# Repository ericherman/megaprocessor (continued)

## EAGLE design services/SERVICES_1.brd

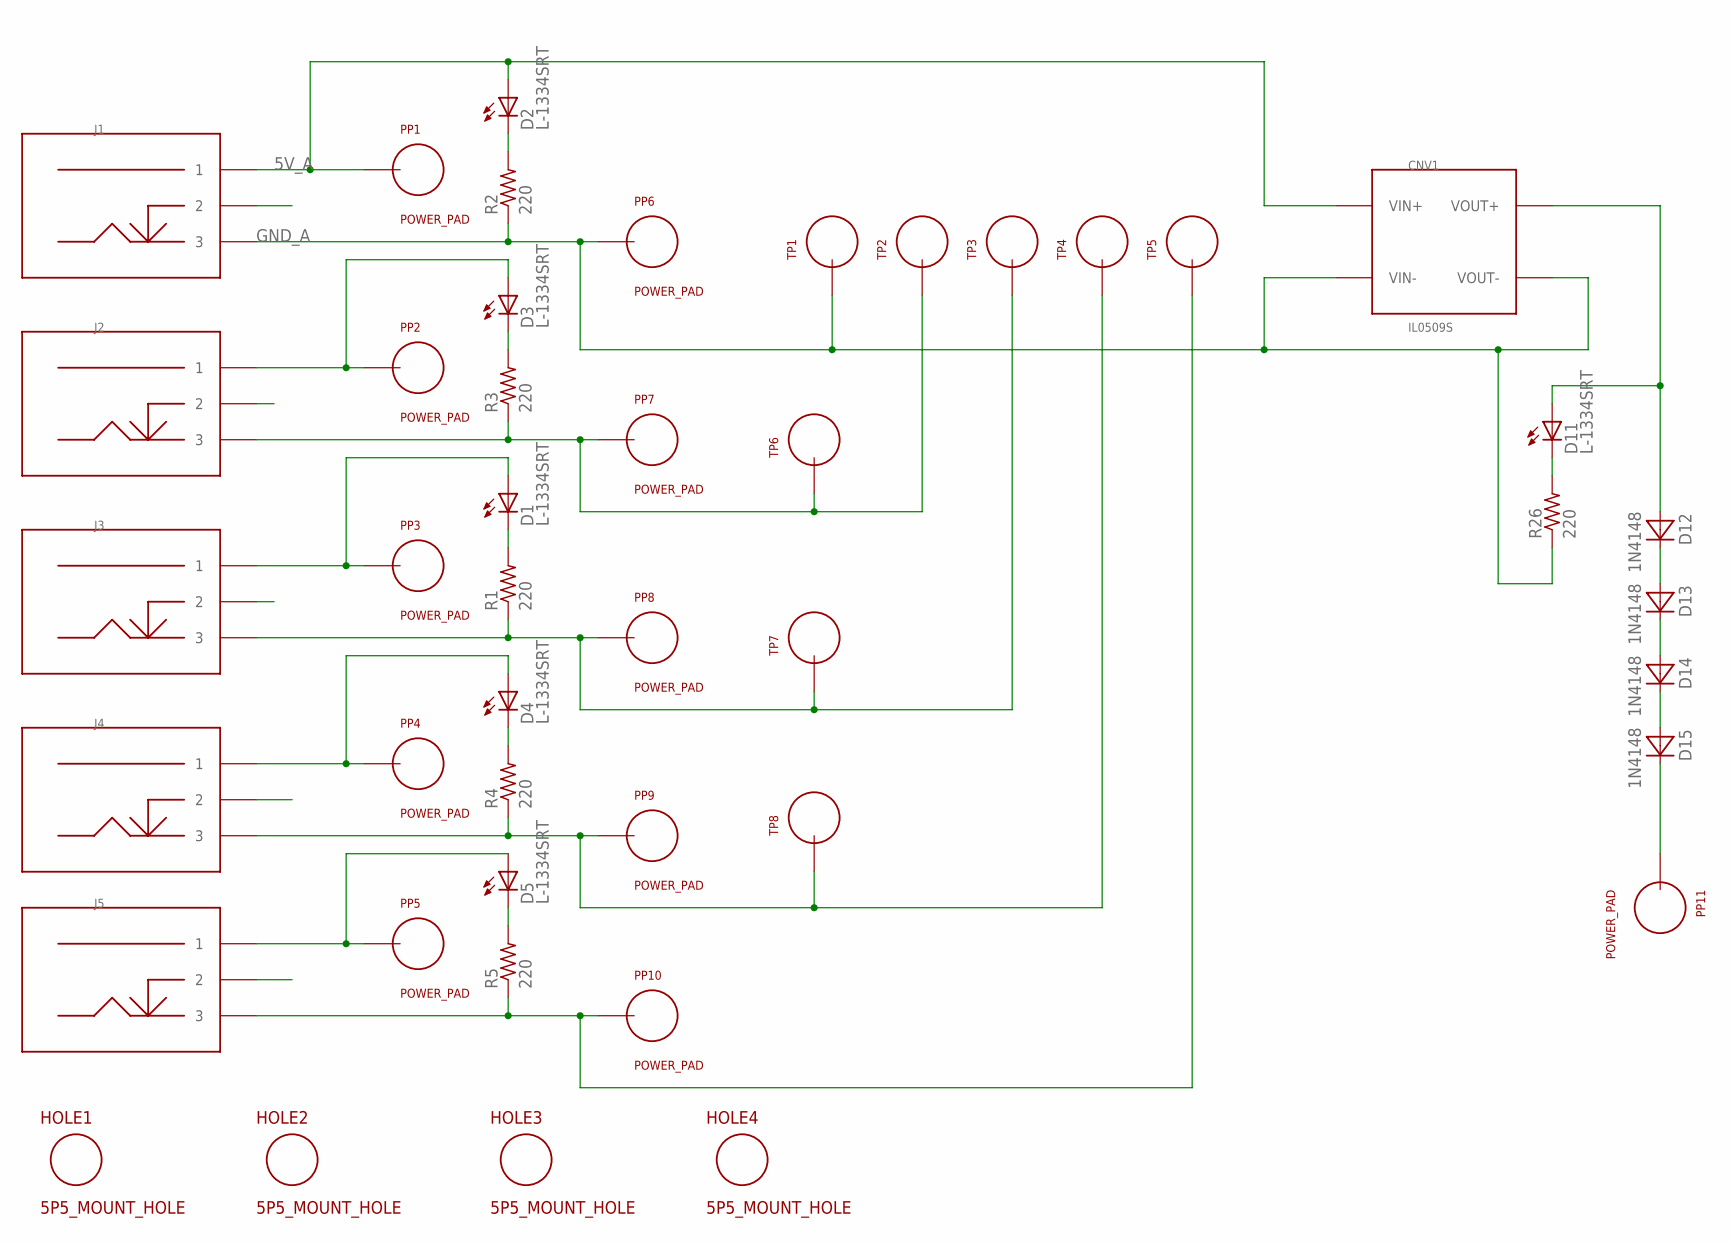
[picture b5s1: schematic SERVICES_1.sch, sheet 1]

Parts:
CNV1: IL0509S; SIL_IL
D1, D2, D3, D4, D5, D11: L-1334SRT; LED3MM
D12, D13, D14, D15: 1N4148; DO34-5
HOLE1, HOLE2, HOLE3, HOLE4: 5P5_MOUNT_HOLE; 5P5M_HOLE
J1, J2, J3, J4, J5: POWER_ENTRY; POWER_25
PP1, PP2, PP3, PP4, PP5, PP6, PP7, PP8, PP9, PP10, PP11: POWER_PAD
R1, R2, R3, R4, R5, R26: 220; R_P2INCH
TP1, TP2, TP3, TP4, TP5, TP6, TP7, TP8: TEST_LOOP

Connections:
5V_A: CNV1.VIN+, D2.A, J1.1, PP1.1; also elsewhere on the board
GND_A: CNV1.VIN-, CNV1.VOUT-, J1.3, PP6.1, R2.1, R26.1, TP1.P$1; also elsewhere on the board
unnamed: D3.A, J2.1, PP2.1
unnamed: D1.A, J3.1, PP3.1
unnamed: D4.A, J4.1, PP4.1
unnamed: D5.A, J5.1, PP5.1
unnamed: J2.3, PP7.1, R3.1, TP2.P$1, TP6.P$1
unnamed: J3.3, PP8.1, R1.1, TP3.P$1, TP7.P$1
unnamed: J4.3, PP9.1, R4.1, TP4.P$1, TP8.P$1
unnamed: J5.3, PP10.1, R5.1, TP5.P$1
unnamed: CNV1.VOUT+, D11.A, D12.A
unnamed: D1.K (C), R1.2
unnamed: D2.K (C), R2.2
unnamed: D3.K (C), R3.2
unnamed: D4.K (C), R4.2
unnamed: D5.K (C), R5.2
unnamed: D11.K (C), R26.2
unnamed: D12.C, D13.A
unnamed: D13.C, D14.A
unnamed: D14.C, D15.A
unnamed: D15.C, PP11.1

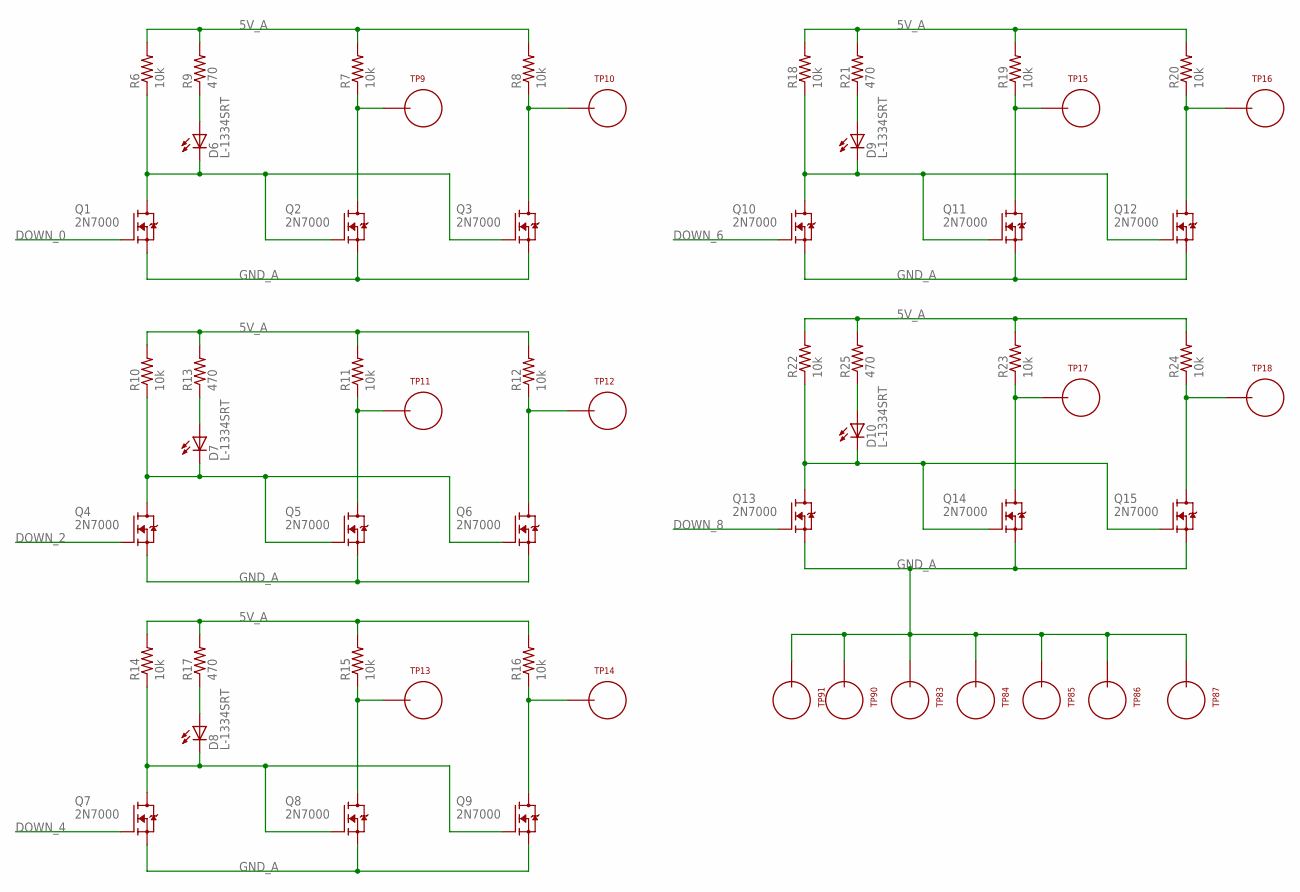
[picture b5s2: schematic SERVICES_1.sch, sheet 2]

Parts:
D6, D7, D8, D9, D10: L-1334SRT; LED3MM
Q1, Q2, Q3, Q4, Q5, Q6, Q7, Q8, Q9, Q10, Q11, Q12, Q13, Q14, Q15: 2N7000; TO92-DGS
R6, R7, R8, R10, R11, R12, R14, R15, R16, R18, R19, R20, R22, R23, R24: 10k; R_P2INCH
R9, R13, R17, R21, R25: 470; R_P2INCH
TP9, TP10, TP11, TP12, TP13, TP14, TP15, TP16, TP17, TP18, TP83, TP84, TP85, TP86, TP87, TP90, TP91: TEST_LOOP

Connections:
5V_A: R6.2, R7.2, R8.2, R9.2, R10.2, R11.2, R12.2, R13.2, R14.2, R15.2, R16.2, R17.2, R18.2, R19.2, R20.2, R21.2, R22.2, R23.2, R24.2, R25.2; also elsewhere on the board
DOWN_0: Q1.G; also elsewhere on the board
DOWN_2: Q4.G; also elsewhere on the board
DOWN_4: Q7.G; also elsewhere on the board
DOWN_6: Q10.G; also elsewhere on the board
DOWN_8: Q13.G; also elsewhere on the board
GND_A: Q1.S, Q2.S, Q3.S, Q4.S, Q5.S, Q6.S, Q7.S, Q8.S, Q9.S, Q10.S, Q11.S, Q12.S, Q13.S, Q14.S, Q15.S, TP83.P$1, TP84.P$1, TP85.P$1, TP86.P$1, TP87.P$1, TP90.P$1, TP91.P$1; also elsewhere on the board
unnamed: D7.A, R13.1
unnamed: Q5.D, R11.1, TP11.P$1
unnamed: Q6.D, R12.1, TP12.P$1
unnamed: D6.A, R9.1
unnamed: Q2.D, R7.1, TP9.P$1
unnamed: Q3.D, R8.1, TP10.P$1
unnamed: D6.K (C), Q1.D, Q2.G, Q3.G, R6.1
unnamed: D7.K (C), Q4.D, Q5.G, Q6.G, R10.1
unnamed: D8.A, R17.1
unnamed: Q8.D, R15.1, TP13.P$1
unnamed: Q9.D, R16.1, TP14.P$1
unnamed: D8.K (C), Q7.D, Q8.G, Q9.G, R14.1
unnamed: D9.A, R21.1
unnamed: Q11.D, R19.1, TP15.P$1
unnamed: Q12.D, R20.1, TP16.P$1
unnamed: D9.K (C), Q10.D, Q11.G, Q12.G, R18.1
unnamed: D10.A, R25.1
unnamed: Q14.D, R23.1, TP17.P$1
unnamed: Q15.D, R24.1, TP18.P$1
unnamed: D10.K (C), Q13.D, Q14.G, Q15.G, R22.1

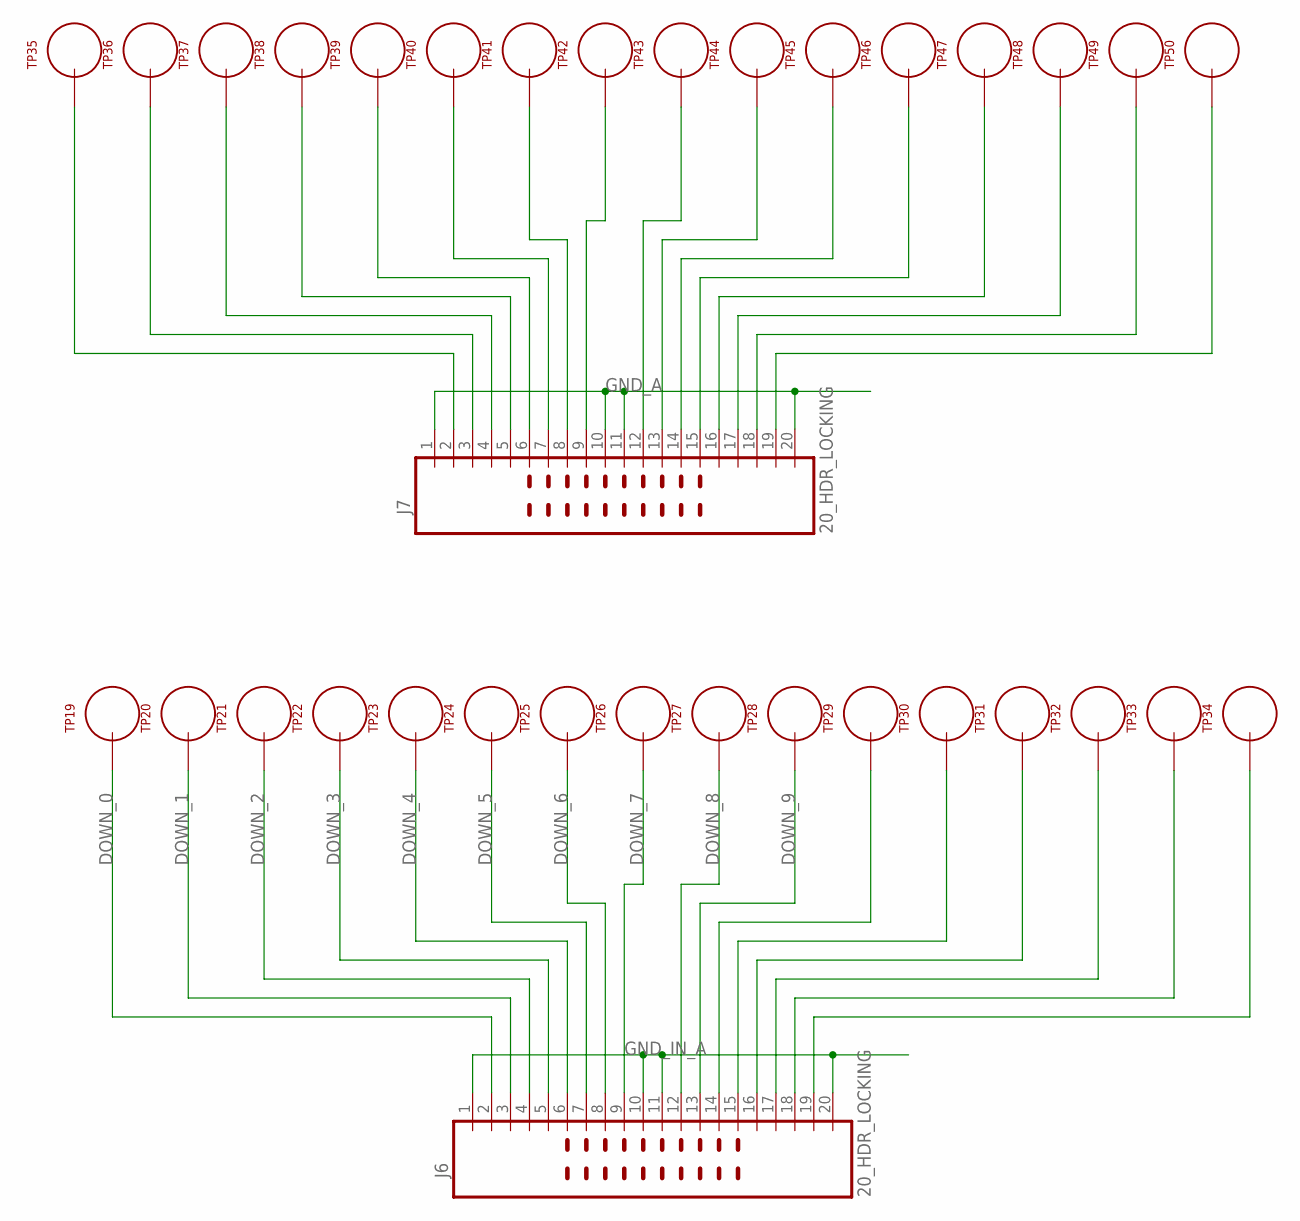
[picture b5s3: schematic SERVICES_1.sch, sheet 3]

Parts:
J6, J7: 20_HDR_LOCKING
TP19, TP20, TP21, TP22, TP23, TP24, TP25, TP26, TP27, TP28, TP29, TP30, TP31, TP32, TP33, TP34, TP35, TP36, TP37, TP38, TP39, TP40, TP41, TP42, TP43, TP44, TP45, TP46, TP47, TP48, TP49, TP50: TEST_LOOP

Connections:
DOWN_0: J6.2, TP19.P$1; also elsewhere on the board
DOWN_1: J6.3, TP20.P$1
DOWN_2: J6.4, TP21.P$1; also elsewhere on the board
DOWN_3: J6.5, TP22.P$1
DOWN_4: J6.6, TP23.P$1; also elsewhere on the board
DOWN_5: J6.7, TP24.P$1
DOWN_6: J6.8, TP25.P$1; also elsewhere on the board
DOWN_7: J6.9, TP26.P$1
DOWN_8: J6.12, TP27.P$1; also elsewhere on the board
DOWN_9: J6.13, TP28.P$1
GND_A: J7.1, J7.10, J7.11, J7.20; also elsewhere on the board
GND_IN_A: J6.1, J6.10, J6.11, J6.20
unnamed: J6.19, TP34.P$1
unnamed: J6.18, TP33.P$1
unnamed: J6.17, TP32.P$1
unnamed: J6.16, TP31.P$1
unnamed: J6.15, TP30.P$1
unnamed: J6.14, TP29.P$1
unnamed: J7.2, TP35.P$1
unnamed: J7.3, TP36.P$1
unnamed: J7.4, TP37.P$1
unnamed: J7.5, TP38.P$1
unnamed: J7.6, TP39.P$1
unnamed: J7.7, TP40.P$1
unnamed: J7.8, TP41.P$1
unnamed: J7.19, TP50.P$1
unnamed: J7.18, TP49.P$1
unnamed: J7.17, TP48.P$1
unnamed: J7.16, TP47.P$1
unnamed: J7.15, TP46.P$1
unnamed: J7.14, TP45.P$1
unnamed: J7.13, TP44.P$1
unnamed: J7.12, TP43.P$1
unnamed: J7.9, TP42.P$1

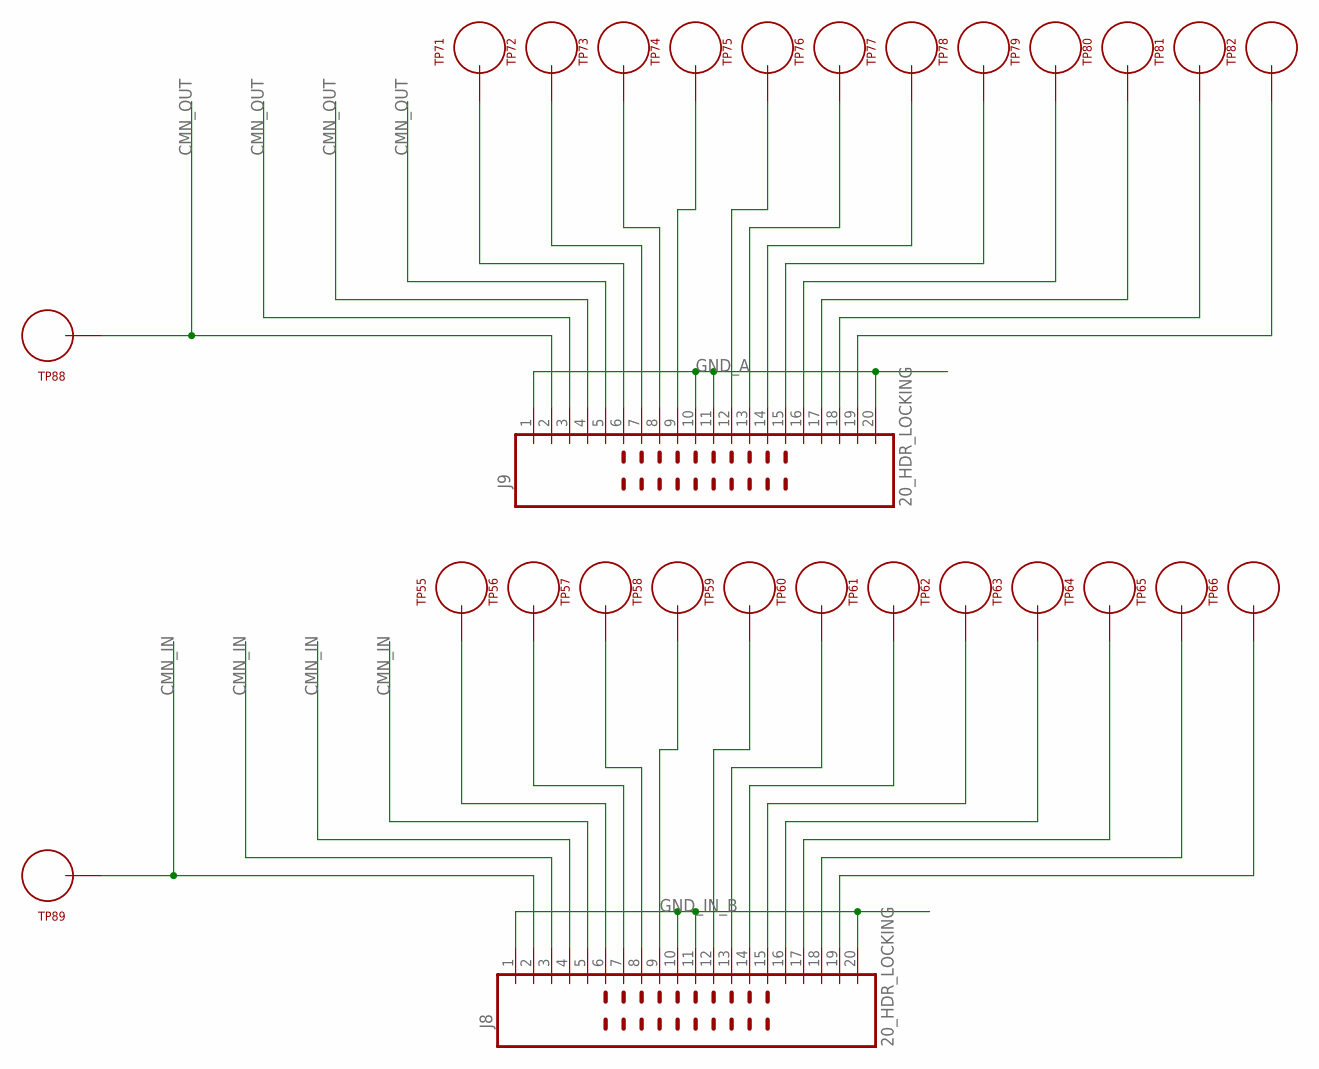
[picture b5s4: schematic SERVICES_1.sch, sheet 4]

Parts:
J8, J9: 20_HDR_LOCKING
TP55, TP56, TP57, TP58, TP59, TP60, TP61, TP62, TP63, TP64, TP65, TP66, TP71, TP72, TP73, TP74, TP75, TP76, TP77, TP78, TP79, TP80, TP81, TP82, TP88, TP89: TEST_LOOP

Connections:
CMN_IN: J8.2, J8.3, J8.4, J8.5, TP89.P$1
CMN_OUT: J9.2, J9.3, J9.4, J9.5, TP88.P$1
GND_A: J9.1, J9.10, J9.11, J9.20; also elsewhere on the board
GND_IN_B: J8.1, J8.10, J8.11, J8.20
unnamed: J8.6, TP55.P$1
unnamed: J8.7, TP56.P$1
unnamed: J8.8, TP57.P$1
unnamed: J8.19, TP66.P$1
unnamed: J8.18, TP65.P$1
unnamed: J8.17, TP64.P$1
unnamed: J8.16, TP63.P$1
unnamed: J8.15, TP62.P$1
unnamed: J8.14, TP61.P$1
unnamed: J8.13, TP60.P$1
unnamed: J8.12, TP59.P$1
unnamed: J8.9, TP58.P$1
unnamed: J9.6, TP71.P$1
unnamed: J9.7, TP72.P$1
unnamed: J9.8, TP73.P$1
unnamed: J9.19, TP82.P$1
unnamed: J9.18, TP81.P$1
unnamed: J9.17, TP80.P$1
unnamed: J9.16, TP79.P$1
unnamed: J9.15, TP78.P$1
unnamed: J9.14, TP77.P$1
unnamed: J9.13, TP76.P$1
unnamed: J9.12, TP75.P$1
unnamed: J9.9, TP74.P$1

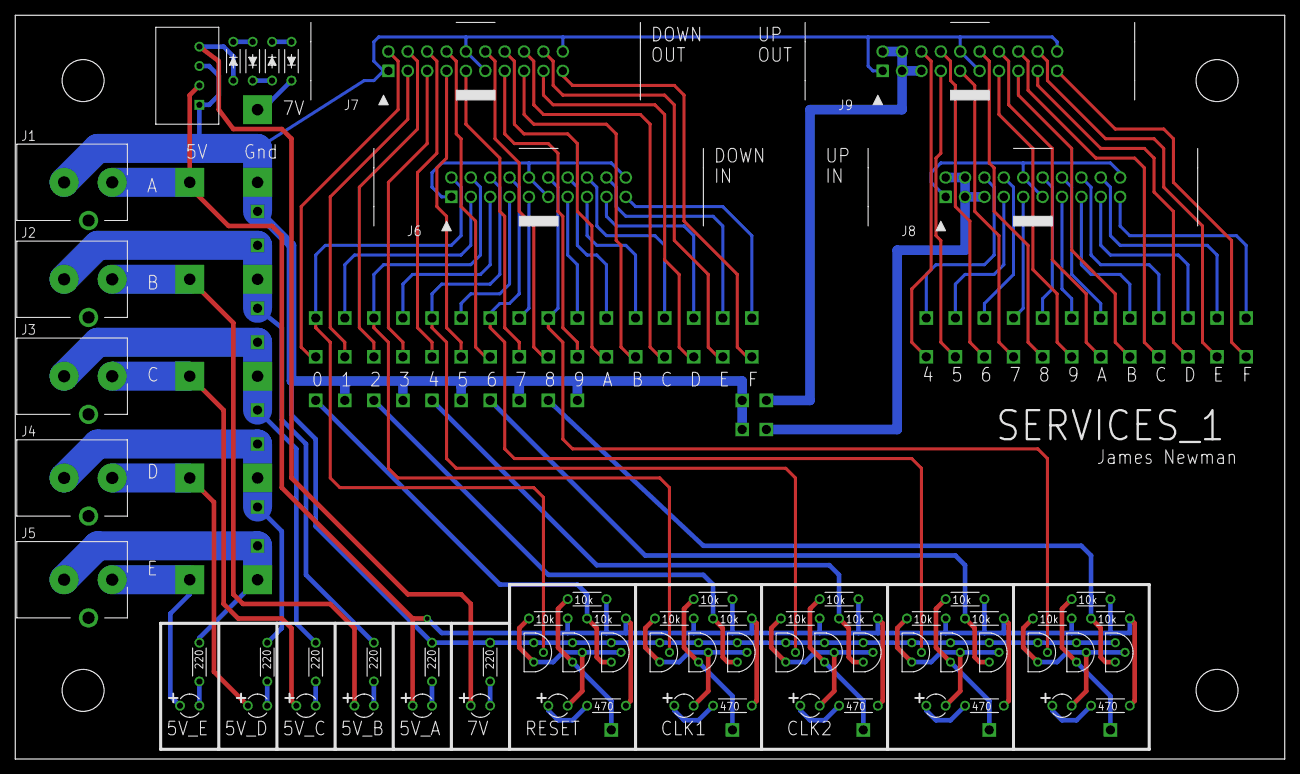
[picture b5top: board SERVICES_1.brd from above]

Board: 2 copper layers, 166.3 x 97.5 mm, 164 parts (0 on the bottom side), 101 nets.

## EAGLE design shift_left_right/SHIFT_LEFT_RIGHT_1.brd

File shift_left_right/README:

Shifter

The shifting is just by wiring from one connector to the other with an
offset. Depending on which side you call the input and which the output
its a left or right shifter. It also generates some status data (is zero
etc).

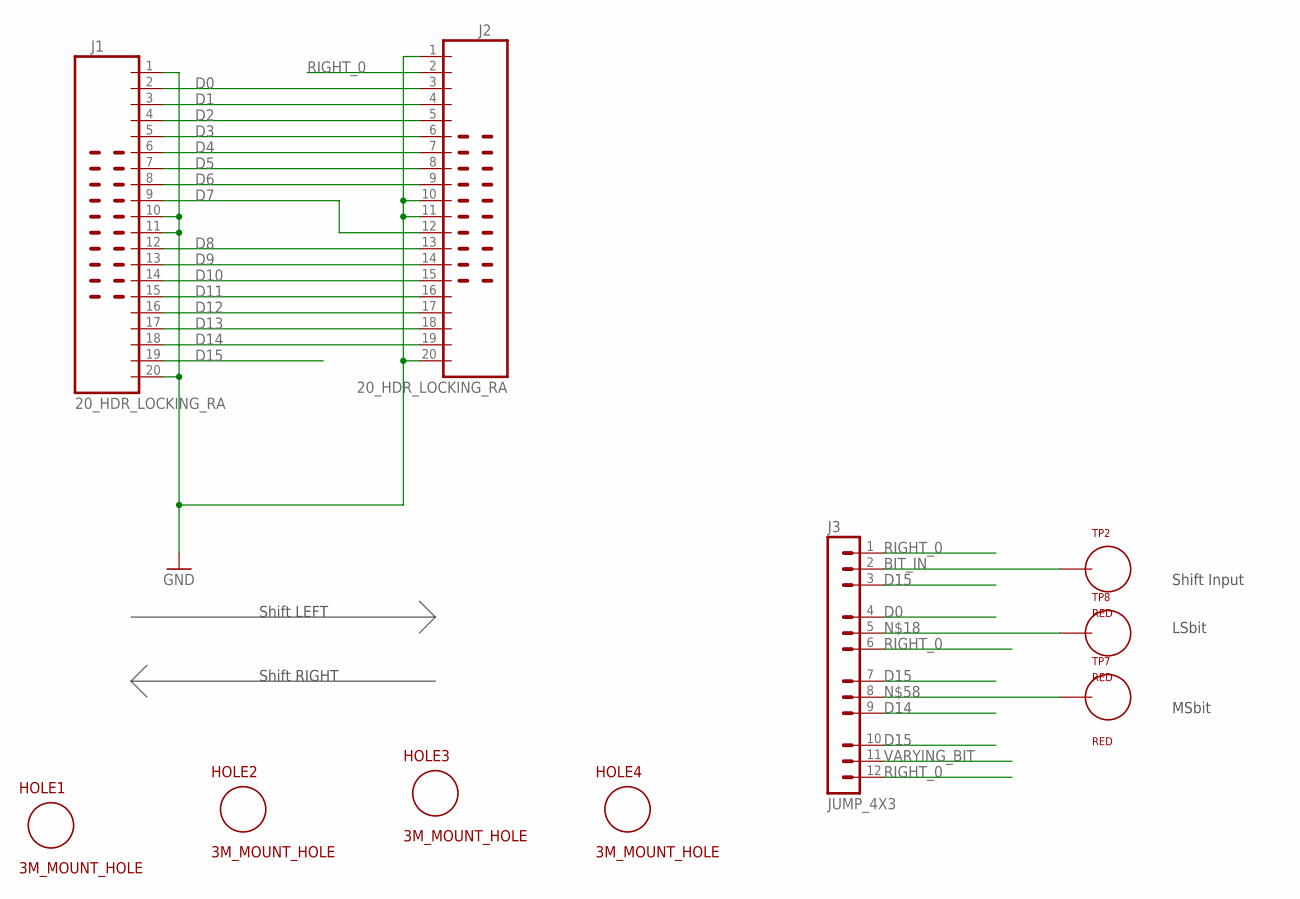
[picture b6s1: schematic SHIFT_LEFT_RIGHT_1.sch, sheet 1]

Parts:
HOLE1, HOLE2, HOLE3, HOLE4: 3M_MOUNT_HOLE; 3M_HOLE
J1, J2: 20_HDR_LOCKING_RA
J3: JUMP_4X3
TP2, TP7, TP8: RED; TEST_LOOP

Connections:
BIT_IN: J3.2, TP2.P$1; also elsewhere on the board
D0: J1.2, J2.3, J3.4; also elsewhere on the board
D1: J1.3, J2.4; also elsewhere on the board
D2: J1.4, J2.5; also elsewhere on the board
D3: J1.5, J2.6; also elsewhere on the board
D4: J1.6, J2.7; also elsewhere on the board
D5: J1.7, J2.8; also elsewhere on the board
D6: J1.8, J2.9; also elsewhere on the board
D7: J1.9, J2.12; also elsewhere on the board
D8: J1.12, J2.13; also elsewhere on the board
D9: J1.13, J2.14; also elsewhere on the board
D10: J1.14, J2.15; also elsewhere on the board
D11: J1.15, J2.16; also elsewhere on the board
D12: J1.16, J2.17; also elsewhere on the board
D13: J1.17, J2.18; also elsewhere on the board
D14: J1.18, J2.19, J3.9; also elsewhere on the board
D15: J1.19, J3.3, J3.7, J3.10; also elsewhere on the board
GND: J1.1, J1.10, J1.11, J1.20, J2.1, J2.10, J2.11, J2.20; also elsewhere on the board
unnamed: J3.5, TP8.P$1
unnamed: J3.8, TP7.P$1
RIGHT_0: J2.2, J3.1, J3.6, J3.12; also elsewhere on the board
VARYING_BIT: J3.11; also elsewhere on the board

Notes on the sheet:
Shift Input
LSbit
MSbit
Shift LEFT
Shift RIGHT

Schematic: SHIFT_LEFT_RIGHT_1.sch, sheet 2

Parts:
C1: 100n; CAP_P2INCH
D1, D2, D3, D5, D6, D7, D8, D9, D27, D28, D29, D30, D31, D32, D33, D34, D35: L-1334SRT; LED3MM
Q1, Q2, Q6, Q7, Q14, Q15, Q16, Q17, Q37: 2N7000; TO92-DGS
R1, R3, R6, R10, R12, R14, R16, R18, R40: 10K; R_P2INCH
R2, R4, R9, R11, R13, R15, R17, R19, R42, R44, R46, R50, R54, R56, R58, R60, R62: 470; R_P2INCH

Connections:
+5V: C1.1, D1.A, D2.A, D3.A, D5.A, D6.A, D7.A, D8.A, D9.A, D27.A, D28.A, D29.A, D30.A, D31.A, D32.A, D33.A, D34.A, D35.A, R1.2, R3.2, R6.2, R10.2, R12.2, R14.2, R16.2, R18.2, R40.2; also elsewhere on the board
D0: Q1.G; also elsewhere on the board
D0_N: Q1.D, R1.1, R2.1, R44.1; also elsewhere on the board
D1: Q2.G; also elsewhere on the board
D1_N: Q2.D, R3.1, R4.1, R46.1; also elsewhere on the board
D2: Q6.G; also elsewhere on the board
D2_N: Q6.D, R6.1, R9.1, R50.1; also elsewhere on the board
D3: Q7.G; also elsewhere on the board
D3_N: Q7.D, R10.1, R11.1, R54.1; also elsewhere on the board
D4: Q14.G; also elsewhere on the board
D4_N: Q14.D, R12.1, R13.1, R56.1; also elsewhere on the board
D5: Q15.G; also elsewhere on the board
D5_N: Q15.D, R14.1, R15.1, R58.1; also elsewhere on the board
D6: Q16.G; also elsewhere on the board
D6_N: Q16.D, R16.1, R17.1, R60.1; also elsewhere on the board
D7: Q17.G; also elsewhere on the board
D7_N: Q17.D, R18.1, R19.1, R62.1; also elsewhere on the board
GND: C1.2, Q1.S, Q2.S, Q6.S, Q7.S, Q14.S, Q15.S, Q16.S, Q17.S, Q37.S; also elsewhere on the board
unnamed: D2.K (C), R4.2
unnamed: D1.K (C), R2.2
unnamed: D28.K (C), R46.2
unnamed: D5.K (C), R11.2
unnamed: D3.K (C), R9.2
unnamed: D27.K (C), R42.2
unnamed: D30.K (C), R54.2
unnamed: D29.K (C), R50.2
unnamed: D6.K (C), R13.2
unnamed: D7.K (C), R15.2
unnamed: D8.K (C), R17.2
unnamed: D9.K (C), R19.2
unnamed: D31.K (C), R56.2
unnamed: D32.K (C), R58.2
unnamed: D33.K (C), R60.2
unnamed: D34.K (C), R62.2
unnamed: D35.K (C), R44.2
RIGHT_0: Q37.G; also elsewhere on the board
RIGHT_0__N: Q37.D, R40.1, R42.1

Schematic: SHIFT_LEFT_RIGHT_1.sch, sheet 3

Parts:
C2: 100n; CAP_P2INCH
D10, D11, D12, D13, D14, D15, D16, D17, D19, D20, D21, D22, D23, D24, D25: L-1334SRT; LED3MM
Q20, Q21, Q24, Q25, Q32, Q33, Q34, Q35: 2N7000; TO92-DGS
R21, R23, R26, R28, R30, R32, R34, R36: 10K; R_P2INCH
R22, R24, R27, R29, R31, R33, R35, R37, R39, R41, R43, R45, R47, R49, R51: 470; R_P2INCH

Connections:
+5V: C2.1, D10.A, D11.A, D12.A, D13.A, D14.A, D15.A, D16.A, D17.A, D19.A, D20.A, D21.A, D22.A, D23.A, D24.A, D25.A, R21.2, R23.2, R26.2, R28.2, R30.2, R32.2, R34.2, R36.2; also elsewhere on the board
D8: Q20.G; also elsewhere on the board
D8_N: Q20.D, R21.1, R22.1, R39.1; also elsewhere on the board
D9: Q21.G; also elsewhere on the board
D9_N: Q21.D, R23.1, R24.1, R41.1; also elsewhere on the board
D10: Q24.G; also elsewhere on the board
D10_N: Q24.D, R26.1, R27.1, R43.1; also elsewhere on the board
D11: Q25.G; also elsewhere on the board
D11_N: Q25.D, R28.1, R29.1, R45.1; also elsewhere on the board
D12: Q32.G; also elsewhere on the board
D12_N: Q32.D, R30.1, R31.1, R47.1; also elsewhere on the board
D13: Q33.G; also elsewhere on the board
D13_N: Q33.D, R32.1, R33.1, R49.1; also elsewhere on the board
D14: Q34.G; also elsewhere on the board
D14_N: Q34.D, R34.1, R35.1, R51.1; also elsewhere on the board
D15: Q35.G; also elsewhere on the board
D15_N: Q35.D, R36.1, R37.1
GND: C2.2, Q20.S, Q21.S, Q24.S, Q25.S, Q32.S, Q33.S, Q34.S, Q35.S; also elsewhere on the board
unnamed: D11.K (C), R24.2
unnamed: D10.K (C), R22.2
unnamed: D20.K (C), R41.2
unnamed: D13.K (C), R29.2
unnamed: D12.K (C), R27.2
unnamed: D19.K (C), R39.2
unnamed: D22.K (C), R45.2
unnamed: D21.K (C), R43.2
unnamed: D14.K (C), R31.2
unnamed: D15.K (C), R33.2
unnamed: D16.K (C), R35.2
unnamed: D17.K (C), R37.2
unnamed: D23.K (C), R47.2
unnamed: D24.K (C), R49.2
unnamed: D25.K (C), R51.2

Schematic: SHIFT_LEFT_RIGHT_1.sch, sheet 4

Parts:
D4, D18: L-1334SRT; LED3MM
Q3, Q4, Q5, Q8, Q9, Q10, Q11, Q12, Q13, Q18, Q19, Q22, Q23, Q26, Q27, Q28, Q29, Q30, Q31, Q36: 2N7000; TO92-DGS
R5, R7, R20, R25: 10K; R_P2INCH
R8, R38: 470; R_P2INCH
TP1: BLACK; TEST_LOOP
TP4: WHITE; TEST_LOOP
TP6: RED; TEST_LOOP

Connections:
+5V: D4.A, D18.A, R5.2, R7.2, R20.2, R25.2, TP6.P$1; also elsewhere on the board
BIT_IN: Q36.G; also elsewhere on the board
D0_N: Q3.G; also elsewhere on the board
D1_N: Q4.G; also elsewhere on the board
D2_N: Q8.G; also elsewhere on the board
D3_N: Q9.G; also elsewhere on the board
D4_N: Q10.G; also elsewhere on the board
D5_N: Q11.G; also elsewhere on the board
D6_N: Q12.G; also elsewhere on the board
D7_N: Q13.G; also elsewhere on the board
D8_N: Q22.G; also elsewhere on the board
D9_N: Q23.G; also elsewhere on the board
D10_N: Q26.G; also elsewhere on the board
D11_N: Q27.G; also elsewhere on the board
D12_N: Q28.G; also elsewhere on the board
D13_N: Q29.G; also elsewhere on the board
D14_N: Q30.G; also elsewhere on the board
GND: Q5.S, Q13.S, Q18.S, Q19.S, Q30.S, Q31.S, Q36.S, TP1.P$1; also elsewhere on the board
LSB_OR: Q3.D, Q5.G, R5.1
MSB_OR: Q18.G, Q22.D, R25.1
unnamed: Q19.D, R8.1, R20.1
unnamed: Q22.S, Q23.D
unnamed: Q23.S, Q26.D
unnamed: Q26.S, Q27.D
unnamed: D4.K (C), R8.2
unnamed: Q5.D, Q18.D, Q19.G, Q31.D, R7.1, TP4.P$1
unnamed: Q3.S, Q4.D
unnamed: Q4.S, Q8.D
unnamed: Q8.S, Q9.D
unnamed: Q9.S, Q10.D
unnamed: Q10.S, Q11.D
unnamed: Q11.S, Q12.D
unnamed: Q12.S, Q13.D
unnamed: Q27.S, Q28.D
unnamed: Q28.S, Q29.D
unnamed: Q29.S, Q30.D
unnamed: D18.K (C), R38.2
unnamed: Q36.D, R38.1
VARYING_BIT: Q31.G; also elsewhere on the board

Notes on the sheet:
LED for y

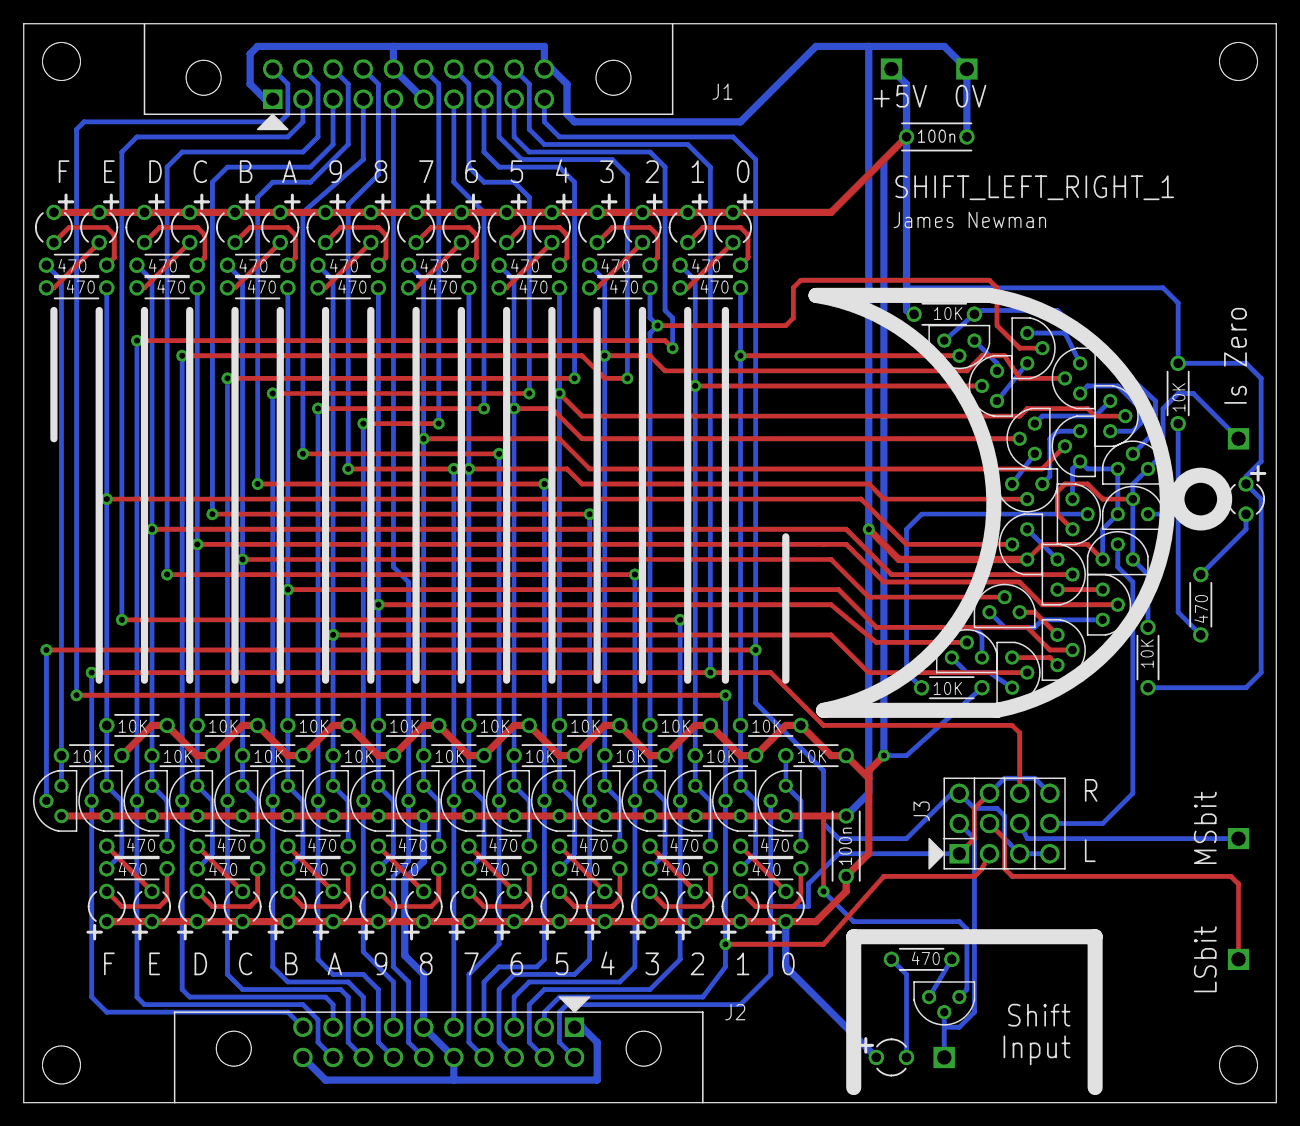
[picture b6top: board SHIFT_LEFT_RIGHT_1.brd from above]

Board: 2 copper layers, 105.4 x 90.8 mm, 141 parts (0 on the bottom side), 92 nets.

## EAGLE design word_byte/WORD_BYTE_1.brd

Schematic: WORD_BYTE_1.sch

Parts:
HOLE1, HOLE2, HOLE3, HOLE4: 3M_MOUNT_HOLE; 3M_HOLE
J1: 20_HDR_LOCKING_RA
J2, J3, J4, J5: 20_HDR_LOCKING
TP1: TEST_LOOP

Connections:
GND: J1.1, J1.10, J1.11, J1.20, J2.1, J2.10, J2.11, J2.20, J3.1, J3.10, J3.11, J3.20, J4.1, J4.10, J4.11, J4.20, J5.1, J5.10, J5.11, J5.20
unnamed: J1.2, J2.2, J3.2
unnamed: J1.13, J4.3, J5.3
unnamed: J1.15, J4.5, J5.5
unnamed: J1.17, J4.7, J5.7
unnamed: J1.19, J4.9, J5.9, TP1.P$1
unnamed: J1.18, J4.8, J5.8
unnamed: J1.16, J4.6, J5.6
unnamed: J1.14, J4.4, J5.4
unnamed: J1.12, J4.2, J5.2
unnamed: J1.9, J2.9, J3.9
unnamed: J1.8, J2.8, J3.8
unnamed: J1.7, J2.7, J3.7
unnamed: J1.6, J2.6, J3.6
unnamed: J1.5, J2.5, J3.5
unnamed: J1.4, J2.4, J3.4
unnamed: J1.3, J2.3, J3.3

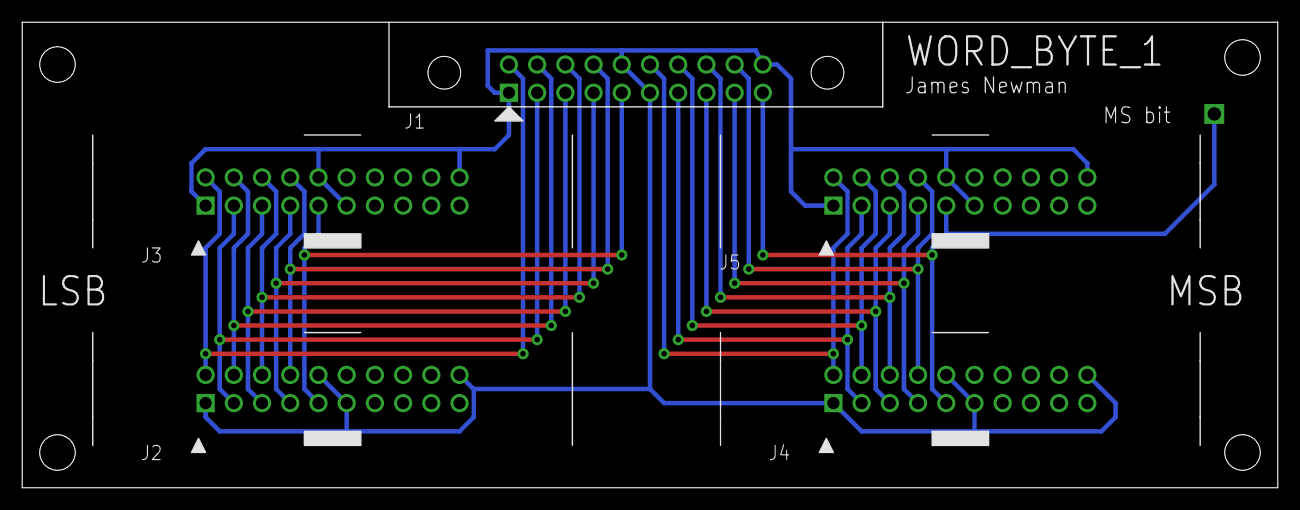
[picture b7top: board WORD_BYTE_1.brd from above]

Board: 2 copper layers, 113.0 x 41.9 mm, 10 parts (0 on the bottom side), 17 nets.
